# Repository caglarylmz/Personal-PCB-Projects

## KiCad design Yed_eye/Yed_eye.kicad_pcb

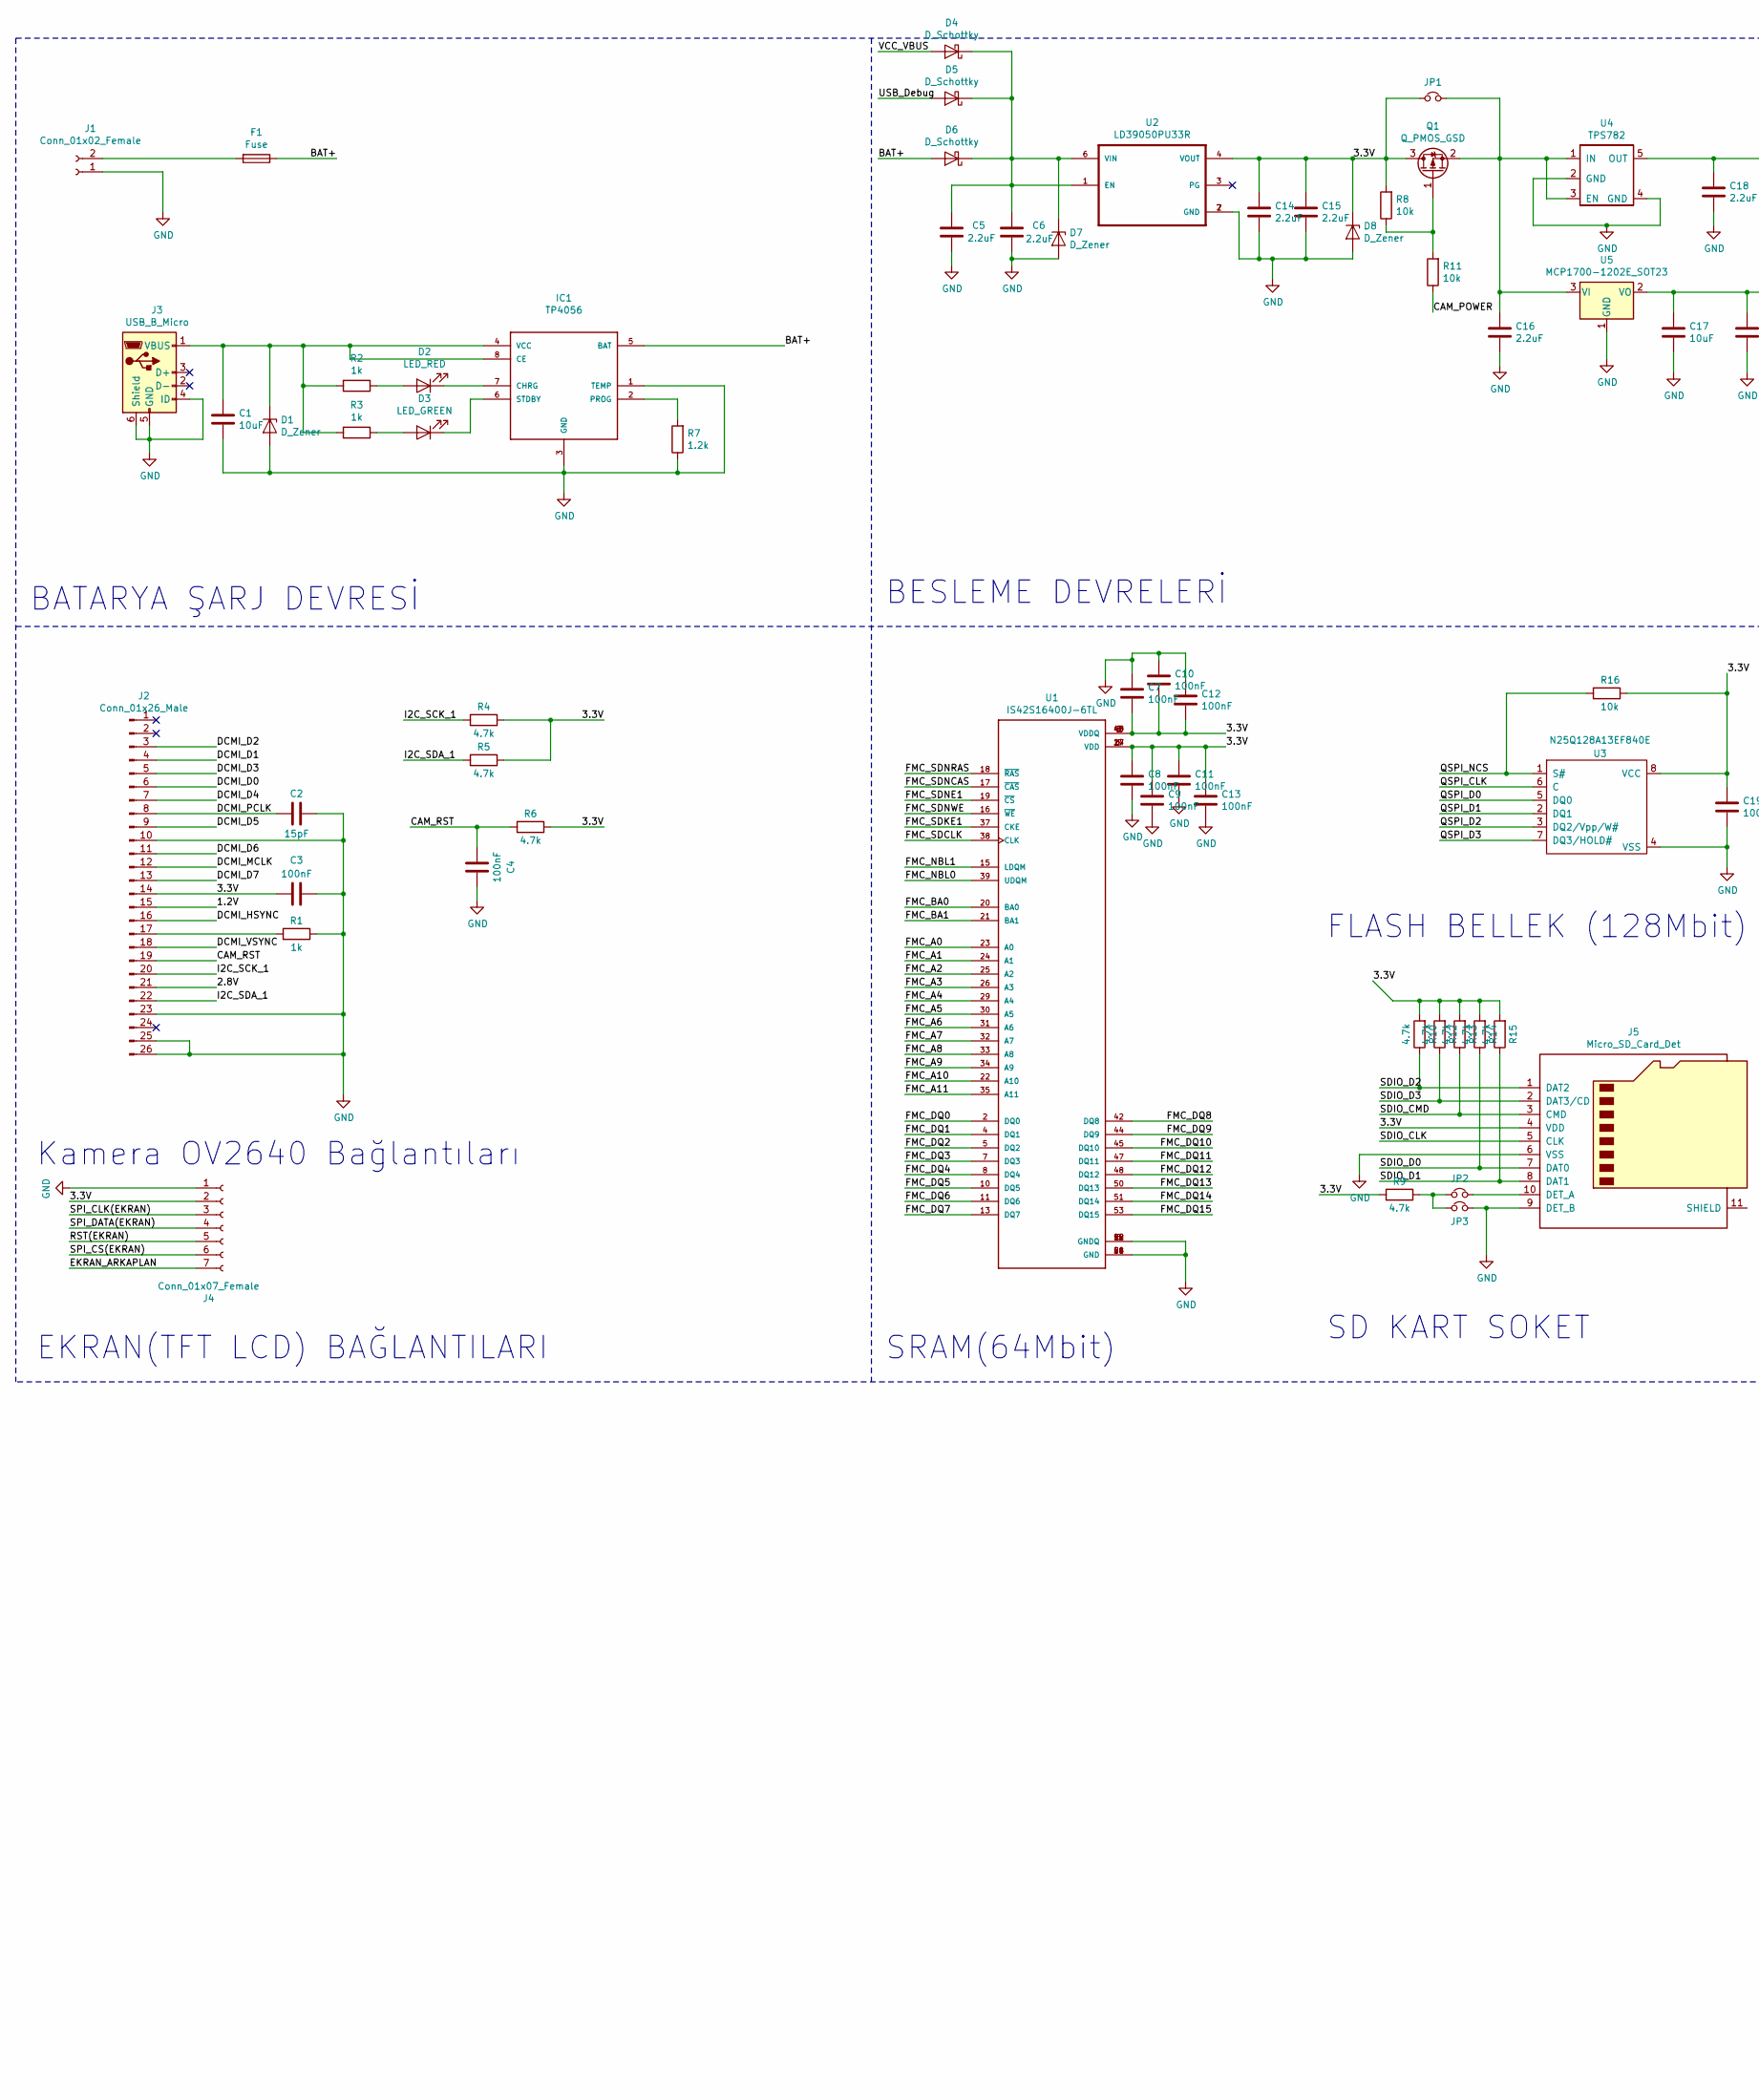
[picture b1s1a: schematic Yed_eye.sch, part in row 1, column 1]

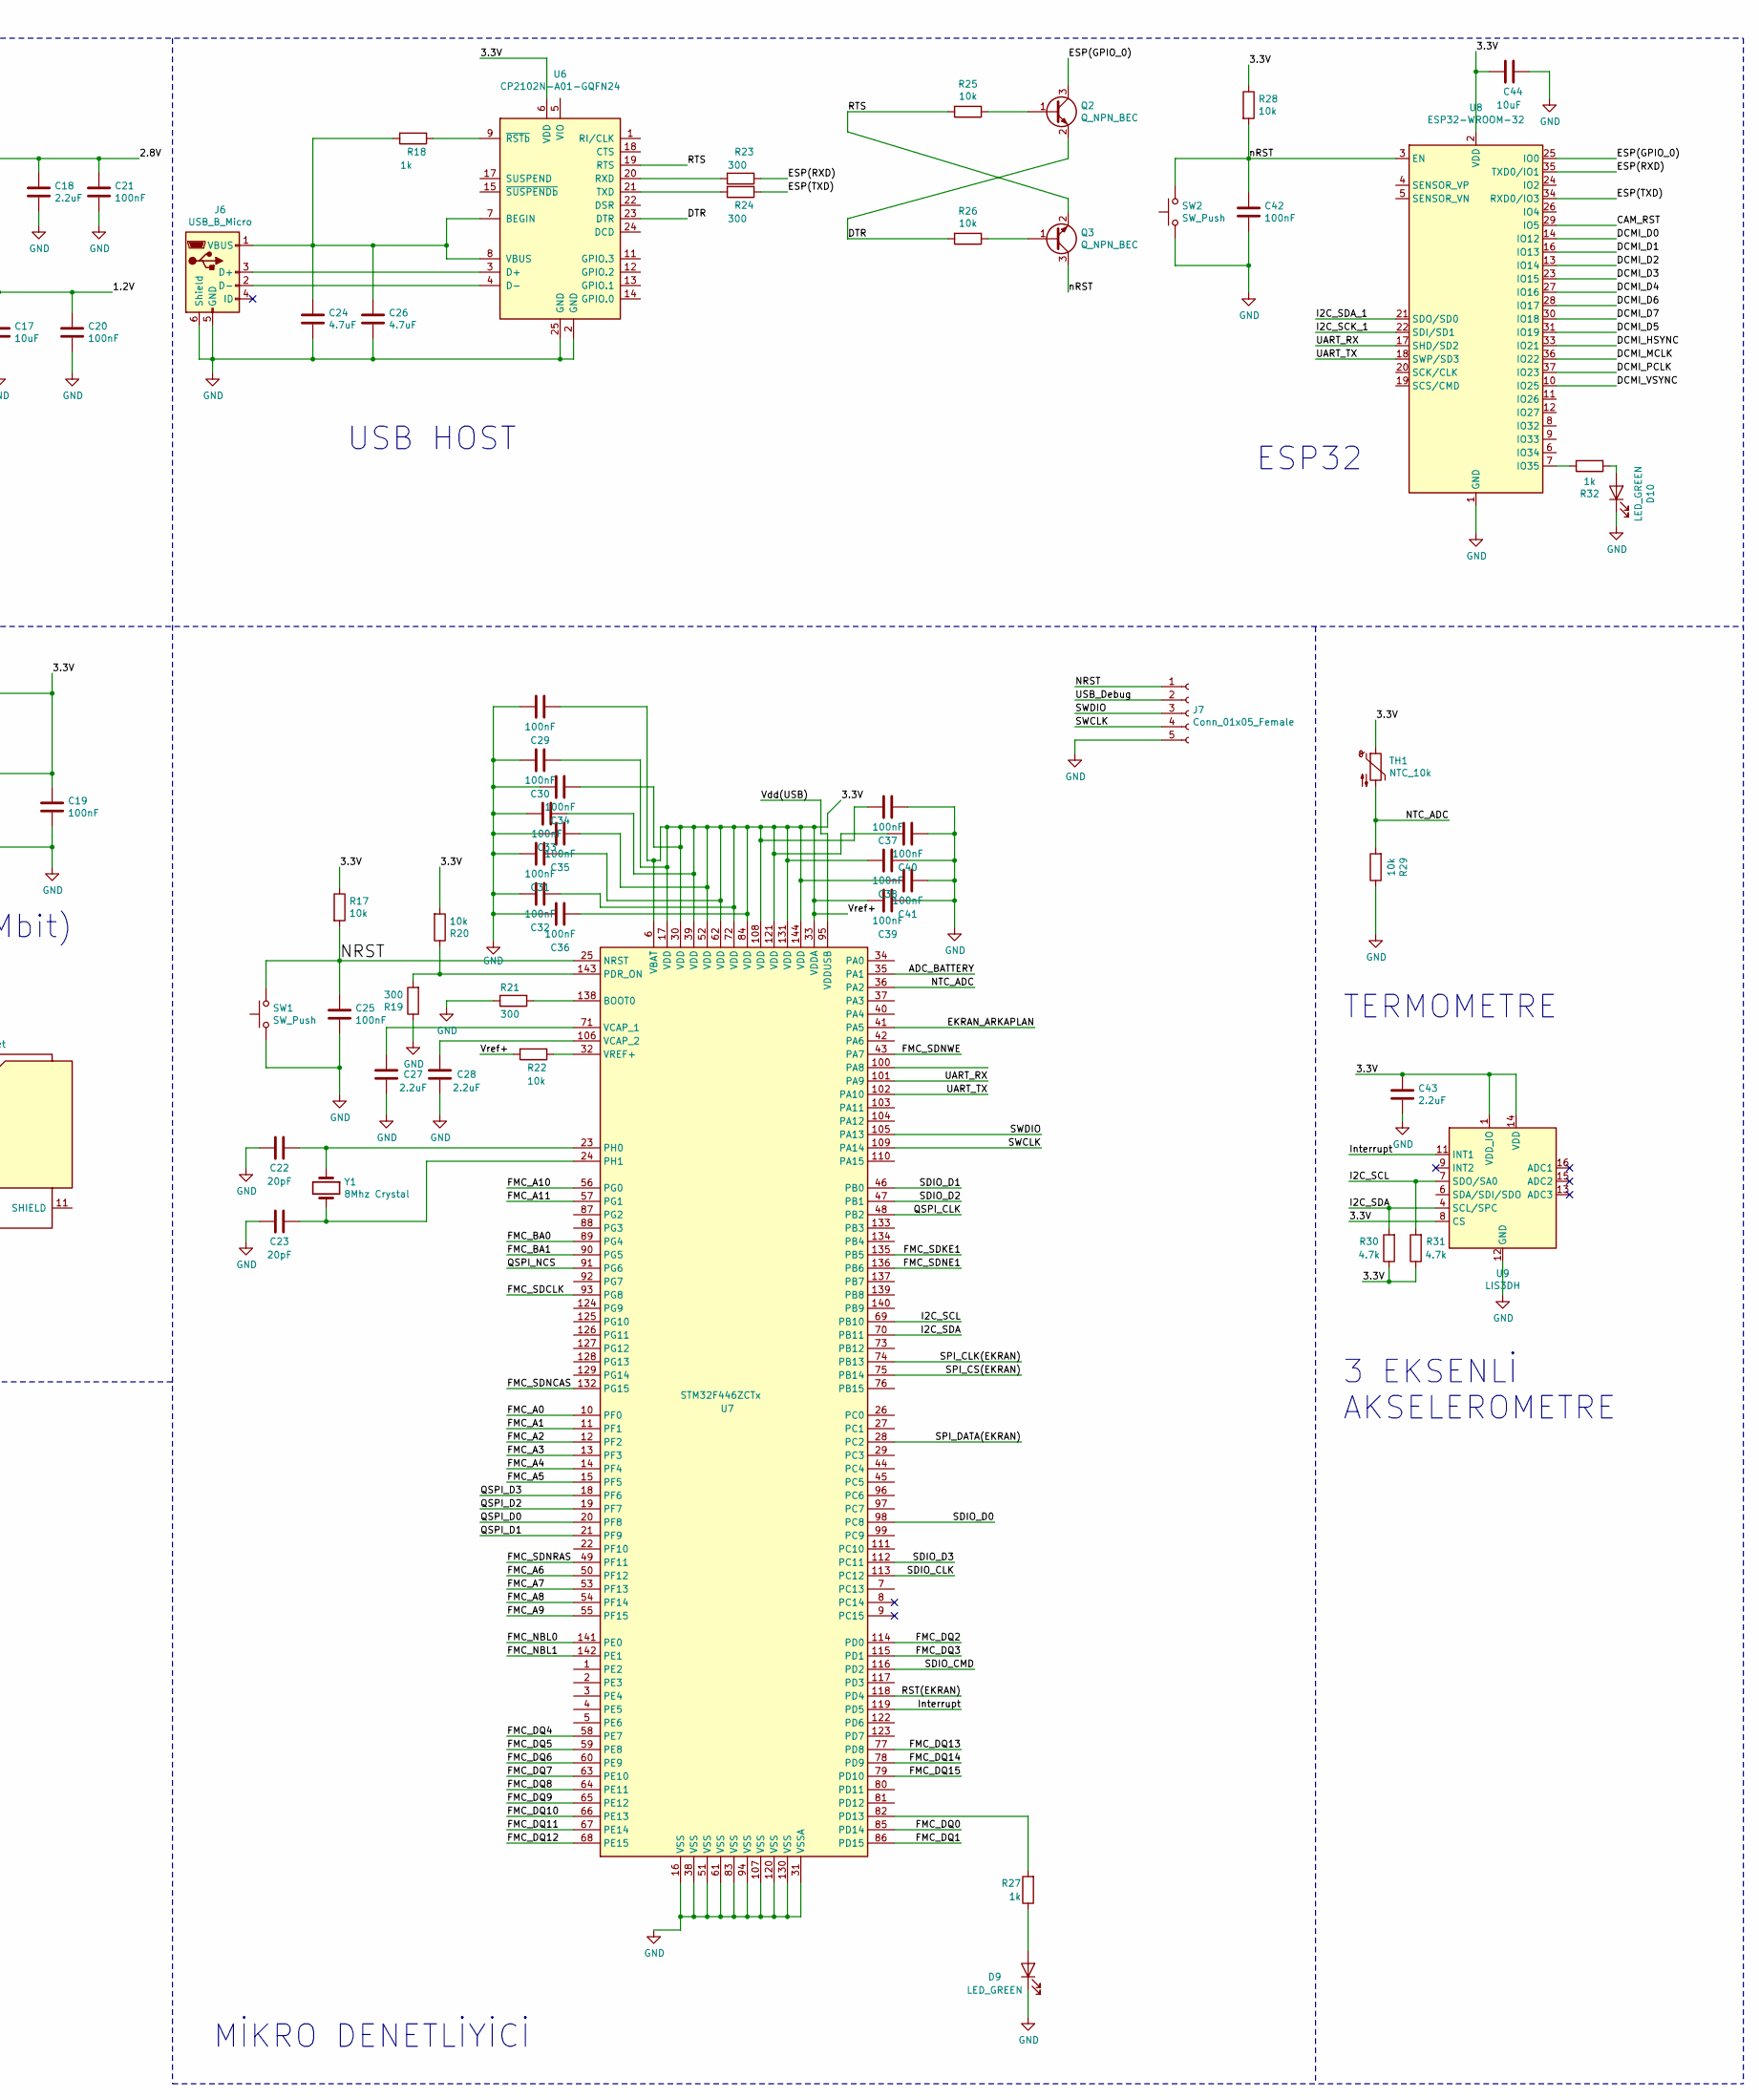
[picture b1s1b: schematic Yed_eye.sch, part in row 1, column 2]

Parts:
C1, C17, C44: 10uF; C_0603_1608Metric_Pad1.05x0.95mm_HandSolder
C2: 15pF; C_0603_1608Metric_Pad1.05x0.95mm_HandSolder
C3, C4, C7, C8, C9, C10, C11, C12, C13, C19, C20, C21, C25, C29, C30, C31, C32, C33, C34, C35, C36, C37, C38, C39, C40, C41, C42: 100nF; C_0603_1608Metric_Pad1.05x0.95mm_HandSolder
C5, C6, C14, C15, C16, C27, C28, C43: 2.2uF; C_0805_2012Metric_Pad1.15x1.40mm_HandSolder
C18: 2.2uF; C_0603_1608Metric_Pad1.05x0.95mm_HandSolder
C22, C23: 20pF; C_0603_1608Metric_Pad1.05x0.95mm_HandSolder
C24, C26: 4.7uF; C_0603_1608Metric_Pad1.05x0.95mm_HandSolder
D1, D7, D8: D_Zener; D_SOD-123
D2: LED_RED; LED_0805_2012Metric_Pad1.15x1.40mm_HandSolder
D3, D9, D10: LED_GREEN; LED_0805_2012Metric_Pad1.15x1.40mm_HandSolder
D4, D5, D6: D_Schottky; D_SOD-123
F1: Fuse; Fuse_1812_4532Metric_Pad1.30x3.40mm_HandSolder
IC1: TP4056; SOP-8_3.76x4.96mm_P1.27mm
J1: Conn_01x02_Female; AMASS_XT30U-F_1x02_P5.0mm_Vertical
J2: Conn_01x26_Male; Hirose_FH12-26S-0.5SH_1x26-1MP_P0.50mm_Horizontal
J3, J6: USB_B_Micro; USB_Micro-B_Molex-105133-0031
J4: Conn_01x07_Female; Molex_200528-0070_1x07-1MP_P1.00mm_Horizontal
J5: Micro_SD_Card_Det; microSD_HC_Hirose_DM3D-SF
J7: Conn_01x05_Female; PinSocket_2x03_P1.27mm_Vertical_SMD
JP1, JP2, JP3: Jumper_NC_Small; SolderJumper-2_P1.3mm_Open_TrianglePad1.0x1.5mm
Q1: Q_PMOS_GSD; SOT-23
Q2, Q3: Q_NPN_BEC; SOT-23
R1, R2, R3, R18, R27, R32: 1k; R_0603_1608Metric_Pad1.05x0.95mm_HandSolder
R4, R5, R6, R9, R10, R12, R13, R14, R15, R30, R31: 4.7k; R_0603_1608Metric_Pad1.05x0.95mm_HandSolder
R7: 1.2k; R_0603_1608Metric_Pad1.05x0.95mm_HandSolder
R8, R11, R16, R17, R20, R22, R25, R26, R28, R29: 10k; R_0603_1608Metric_Pad1.05x0.95mm_HandSolder
R19, R21, R23, R24: 300; R_0603_1608Metric_Pad1.05x0.95mm_HandSolder
SW1: SW_Push; SW_PUSH_6mm_H4.3mm
SW2: SW_Push; SW_PUSH_6mm_H5mm
TH1: NTC_10k; R_0603_1608Metric_Pad1.05x0.95mm_HandSolder
U1: IS42S16400J-6TL; SOP80P1176X120-54N
U2: LD39050PU33R; DFN-6-1EP_3x3mm_P1mm_EP1.5x2.4mm
U3: N25Q128A13EF840E; DFN-8-1EP_6x5mm_P1.27mm_EP2x2mm
U4: TPS782; SOT-23-5_HandSoldering
U5: MCP1700-1202E_SOT23; SOT-23
U6: CP2102N-A01-GQFN24; QFN-24-1EP_4x4mm_P0.5mm_EP2.6x2.6mm
U7: STM32F446ZCTx; LQFP-144_20x20mm_P0.5mm
U8: ESP32-WROOM-32
U9: LIS3DH; LGA-16_3x3mm_P0.5mm_LayoutBorder3x5y
Y1: 8Mhz Crystal; Crystal_SMD_3215-2Pin_3.2x1.5mm

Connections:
/1.2V: C17.1, C20.1, J2.15, U5.2 (VO)
/2.8V: C18.1, C21.1, J2.21, U4.5 (OUT)
/3.3V: C3.2, C7.2, C8.1, C9.1, C10.2, C11.1, C12.2, C13.1, C14.1, C15.1, C19.1, C29.2, C30.2, C31.2, C32.2, C33.2, C34.2, C35.2, C36.2, C37.1, C38.1, C39.1, C40.1, C41.1, C43.1, C44.2, D8.1 (K), J2.14, J4.2, J5.4 (VDD), JP1.1, Q1.3 (D), R4.1, R5.1, R6.1, R8.2, R9.2, R10.2, R12.2, R13.2, R14.2, R15.2, R16.1, R17.1, R20.2, R22.2, R28.1, R30.1, R31.1, TH1.1, U1.1 (VDD), U1.3 (VDDQ), U1.9 (VDDQ), U1.14 (VDD), U1.27 (VDD), U1.43 (VDDQ), U1.49 (VDDQ), U2.4 (VOUT), U3.8 (VCC), U6.6 (VDD), U7.6 (VBAT), U7.17 (VDD), U7.30 (VDD), U7.33 (VDDA), U7.39 (VDD), U7.52 (VDD), U7.62 (VDD), U7.72 (VDD), U7.84 (VDD), U7.108 (VDD), U7.121 (VDD), U7.131 (VDD), U7.144 (VDD), U8.2 (VDD), U9.1 (VDD_IO), U9.8 (CS), U9.14 (VDD)
/BAT+: D6.2 (A), F1.1, IC1.5 (BAT)
/CAM_RST: C4.2, J2.19, R6.2, U8.29 (IO5)
/DCMI_D0: J2.6, U8.14 (IO12)
/DCMI_D1: J2.4, U8.16 (IO13)
/DCMI_D2: J2.3, U8.13 (IO14)
/DCMI_D3: J2.5, U8.23 (IO15)
/DCMI_D4: J2.7, U8.27 (IO16)
/DCMI_D5: J2.9, U8.31 (IO19)
/DCMI_D6: J2.11, U8.28 (IO17)
/DCMI_D7: J2.13, U8.30 (IO18)
/DCMI_HSYNC: J2.16, U8.33 (IO21)
/DCMI_MCLK: J2.12, U8.36 (IO22)
/DCMI_PCLK: C2.2, J2.8, U8.37 (IO23)
/DCMI_VSYNC: J2.18, U8.10 (IO25)
/DTR: Q2.2 (E), R26.2, U6.23 (DTR)
/EKRAN_ARKAPLAN: J4.7, U7.41 (PA5)
/ESP(GPIO_0): Q2.3 (C), U8.25 (IO0)
/ESP(RXD): R23.1, U8.35 (TXD0/IO1)
/ESP(TXD): R24.1, U8.34 (RXD0/IO3)
/FMC_A0: U1.23 (A0), U7.10 (PF0)
/FMC_A1: U1.24 (A1), U7.11 (PF1)
/FMC_A2: U1.25 (A2), U7.12 (PF2)
/FMC_A3: U1.26 (A3), U7.13 (PF3)
/FMC_A4: U1.29 (A4), U7.14 (PF4)
/FMC_A5: U1.30 (A5), U7.15 (PF5)
/FMC_A6: U1.31 (A6), U7.50 (PF12)
/FMC_A7: U1.32 (A7), U7.53 (PF13)
/FMC_A8: U1.33 (A8), U7.54 (PF14)
/FMC_A9: U1.34 (A9), U7.55 (PF15)
/FMC_A10: U1.22 (A10), U7.56 (PG0)
/FMC_A11: U1.35 (A11), U7.57 (PG1)
/FMC_BA0: U1.20 (BA0), U7.89 (PG4)
/FMC_BA1: U1.21 (BA1), U7.90 (PG5)
/FMC_DQ0: U1.2 (DQ0), U7.85 (PD14)
/FMC_DQ1: U1.4 (DQ1), U7.86 (PD15)
/FMC_DQ2: U1.5 (DQ2), U7.114 (PD0)
/FMC_DQ3: U1.7 (DQ3), U7.115 (PD1)
/FMC_DQ4: U1.8 (DQ4), U7.58 (PE7)
/FMC_DQ5: U1.10 (DQ5), U7.59 (PE8)
/FMC_DQ6: U1.11 (DQ6), U7.60 (PE9)
/FMC_DQ7: U1.13 (DQ7), U7.63 (PE10)
/FMC_DQ8: U1.42 (DQ8), U7.64 (PE11)
/FMC_DQ9: U1.44 (DQ9), U7.65 (PE12)
/FMC_DQ10: U1.45 (DQ10), U7.66 (PE13)
/FMC_DQ11: U1.47 (DQ11), U7.67 (PE14)
/FMC_DQ12: U1.48 (DQ12), U7.68 (PE15)
/FMC_DQ13: U1.50 (DQ13), U7.77 (PD8)
/FMC_DQ14: U1.51 (DQ14), U7.78 (PD9)
/FMC_DQ15: U1.53 (DQ15), U7.79 (PD10)
/FMC_NBL0: U1.39 (UDQM), U7.141 (PE0)
/FMC_NBL1: U1.15 (LDQM), U7.142 (PE1)
/FMC_SDCLK: U1.38 (CLK), U7.93 (PG8)
/FMC_SDKE1: U1.37 (CKE), U7.135 (PB5)
/FMC_SDNCAS: U1.17 (~CAS~), U7.132 (PG15)
/FMC_SDNE1: U1.19 (~CS~), U7.136 (PB6)
/FMC_SDNRAS: U1.18 (~RAS~), U7.49 (PF11)
/FMC_SDNWE: U1.16 (~WE~), U7.43 (PA7)
/I2C_SCK_1: J2.20, R4.2, U8.22 (SDI/SD1)
/I2C_SCL: R31.2, U7.69 (PB10), U9.7 (SDO/SA0)
/I2C_SDA: R30.2, U7.70 (PB11), U9.4 (SCL/SPC)
/I2C_SDA_1: J2.22, R5.2, U8.21 (SDO/SD0)
/Interrupt: U7.119 (PD5), U9.11 (INT1)
/NRST: C25.1, J7.1, R17.2, SW1.2, U7.25 (NRST)
/NTC_ADC: R29.2, TH1.2, U7.36 (PA2)
/QSPI_CLK: U3.6 (C), U7.48 (PB2)
/QSPI_D0: U3.5 (DQ0), U7.20 (PF8)
/QSPI_D1: U3.2 (DQ1), U7.21 (PF9)
/QSPI_D2: U3.3 (DQ2/Vpp/W#), U7.19 (PF7)
/QSPI_D3: U3.7 (DQ3/HOLD#), U7.18 (PF6)
/QSPI_NCS: R16.2, U3.1 (S#), U7.91 (PG6)
/RST(EKRAN): J4.5, U7.118 (PD4)
/RTS: Q3.2 (E), R25.2, U6.19 (RTS)
/SDIO_CLK: J5.5 (CLK), U7.113 (PC12)
/SDIO_CMD: J5.3 (CMD), R13.1, U7.116 (PD2)
/SDIO_D0: J5.7 (DAT0), R14.1, U7.98 (PC8)
/SDIO_D1: J5.8 (DAT1), R15.1, U7.46 (PB0)
/SDIO_D2: J5.1 (DAT2), R10.1, U7.47 (PB1)
/SDIO_D3: J5.2 (DAT3/CD), R12.1, U7.112 (PC11)
/SPI_CLK(EKRAN): J4.3, U7.74 (PB13)
/SPI_CS(EKRAN): J4.6, U7.75 (PB14)
/SPI_DATA(EKRAN): J4.4, U7.28 (PC2)
/SWCLK: J7.4, U7.109 (PA14)
/SWDIO: J7.3, U7.105 (PA13)
/UART_RX: U7.101 (PA9), U8.17 (SHD/SD2)
/UART_TX: U7.102 (PA10), U8.18 (SWP/SD3)
/USB_Debug: D5.2 (A), J7.2
/nRST: C42.1, Q3.3 (C), R28.2, SW2.2, U8.3 (EN)
GND: C1.2, C2.1, C3.1, C4.1, C5.2, C6.2, C7.1, C8.2, C9.2, C10.1, C11.2, C12.1, C13.2, C14.2, C15.2, C16.2, C17.2, C18.2, C19.2, C20.2, C21.2, C22.2, C23.2, C24.2, C25.2, C26.2, C27.2, C28.2, C29.1, C30.1, C31.1, C32.1, C33.1, C34.1, C35.1, C36.1, C37.2, C38.2, C39.2, C40.2, C41.2, C42.2, C43.2, C44.1, D1.2 (A), D7.2 (A), D8.2 (A), D9.1 (K), D10.1 (K), IC1.1 (TEMP), IC1.3 (GND), J1.1, J2.10, J2.23, J2.25, J2.26, J3.4 (ID), J3.5 (GND), J3.6 (Shield), J4.1, J5.6 (VSS), J5.9 (DET_B), J6.5 (GND), J6.6 (Shield), J7.5, JP3.2, R1.1, R7.1, R19.1, R21.1, R29.1, SW1.1, SW2.1, U1.6 (GNDQ), U1.12 (GNDQ), U1.28 (GND), U1.41 (GND), U1.46 (GNDQ), U1.52 (GNDQ), U1.54 (GND), U2.2 (GND), U2.7 (GND), U3.4 (VSS), U4.2 (GND), U4.4 (GND), U5.1 (GND), U6.2 (GND), U6.25 (GND), U7.16 (VSS), U7.31 (VSSA), U7.38 (VSS), U7.51 (VSS), U7.61 (VSS), U7.83 (VSS), U7.94 (VSS), U7.107 (VSS), U7.120 (VSS), U7.130 (VSS), U8.1 (GND), U8.15 (GND), U8.38 (GND), U9.5 (GND), U9.10 (GND), U9.12 (GND)
unnamed: C1.1, D1.1 (K), IC1.4 (VCC), IC1.8 (CE), J3.1 (VBUS), R2.2, R3.2
unnamed: C5.1, C6.1, D4.1 (K), D5.1 (K), D6.1 (K), D7.1 (K), U2.1 (EN), U2.6 (VIN)
unnamed: C16.1, JP1.2, Q1.2 (S), U4.1 (IN), U4.3 (EN), U5.3 (VI)
unnamed: C22.1, U7.23 (PH0), Y1.1
unnamed: C23.1, U7.24 (PH1), Y1.2
unnamed: C24.1, C26.1, J6.1 (VBUS), R18.2, U6.7 (BEGIN), U6.8 (VBUS)
unnamed: C27.1, U7.71 (VCAP_1)
unnamed: C28.1, U7.106 (VCAP_2)
unnamed: D2.1 (K), IC1.7 (CHRG)
unnamed: D2.2 (A), R2.1
unnamed: D3.1 (K), IC1.6 (STDBY)
unnamed: D3.2 (A), R3.1
unnamed: D9.2 (A), R27.1
unnamed: D10.2 (A), R32.2
unnamed: F1.2, J1.2
unnamed: IC1.2 (PROG), R7.2
unnamed: J2.17, R1.2
unnamed: J5.10 (DET_A), JP2.2
unnamed: J6.2 (D-), U6.4 (D-)
unnamed: J6.3 (D+), U6.3 (D+)
unnamed: JP2.1, JP3.1, R9.1
unnamed: Q1.1 (G), R8.1, R11.2
unnamed: Q2.1 (B), R25.1
unnamed: Q3.1 (B), R26.1
unnamed: R18.1, U6.9 (~RSTb)
unnamed: R19.2, R20.1, U7.143 (PDR_ON)
unnamed: R21.2, U7.138 (BOOT0)
unnamed: R22.1, U7.32 (VREF+)
unnamed: R23.2, U6.20 (RXD)
unnamed: R24.2, U6.21 (TXD)
unnamed: R27.2, U7.82 (PD13)
unnamed: R32.1, U8.7 (IO35)

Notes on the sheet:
Kamera OV2640 Bağlantıları
FLASH BELLEK (128Mbit)
SRAM(64Mbit)
BATARYA ŞARJ DEVRESİ
BESLEME DEVRELERİ
USB HOST
SD KART SOKET
MİKRO DENETLİYİCİ
TERMOMETRE
3 EKSENLİ AKSELEROMETRE
ESP32
EKRAN(TFT LCD) BAĞLANTILARI

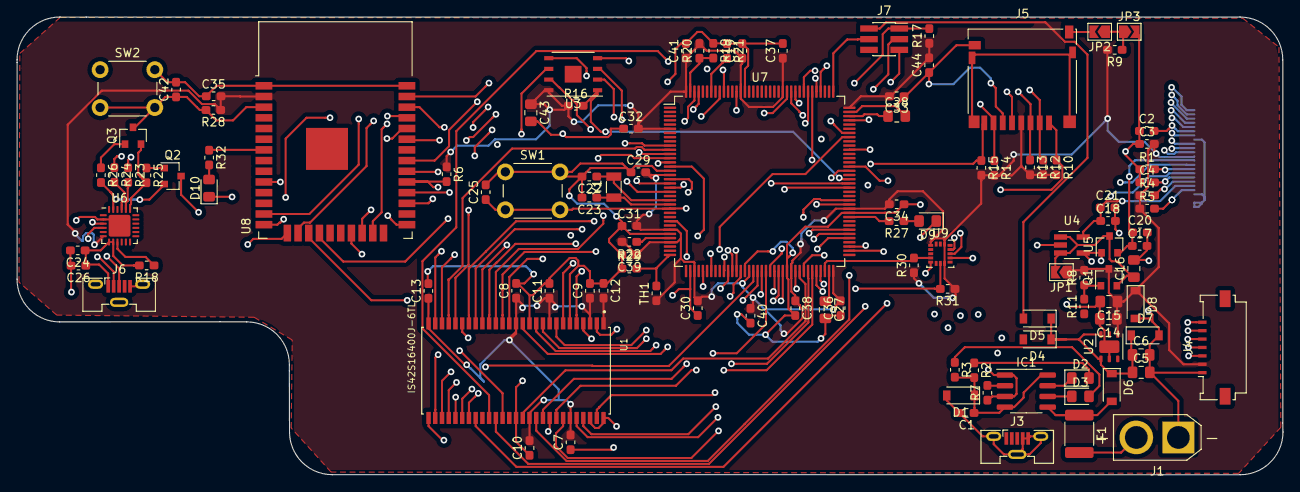
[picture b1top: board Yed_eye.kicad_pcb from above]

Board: 4 copper layers, 150.5 x 54.4 mm, 114 parts (1 on the bottom side), 123 nets.

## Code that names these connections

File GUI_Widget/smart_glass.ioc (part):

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Mcu.Name=STM32F446Z(C-E)Tx
Mcu.Package=LQFP144
Mcu.UserName=STM32F446ZCTx
PA1.GPIOParameters=GPIO_Label
PA1.GPIO_Label=ADC_BAT
PA1.Signal=ADCx_IN1
PA10.Mode=Asynchronous
PA10.Signal=USART1_RX
PA13.Mode=Serial_Wire
PA13.Signal=SYS_JTMS-SWDIO
PA14.Mode=Serial_Wire
PA14.Signal=SYS_JTCK-SWCLK
PA2.GPIOParameters=GPIO_Label
PA2.GPIO_Label=ADC_NTC
PA2.Signal=ADCx_IN2
PA4.Mode=Slave_8_bits_External_Synchro
PA4.Signal=DCMI_HSYNC
PA5.Signal=COMP_DAC2_group
PA6.Mode=Slave_8_bits_External_Synchro
PA6.Signal=DCMI_PIXCLK
PA7.Signal=FMC_SDNWE
PA8.Mode=Clock-out-1
PA8.Signal=RCC_MCO_1
PA9.Mode=Asynchronous
PA9.Signal=USART1_TX
PB0.Mode=SD_4_bits_Wide_bus
PB0.Signal=SDIO_D1
PB1.Mode=SD_4_bits_Wide_bus
PB1.Signal=SDIO_D2
PB10.Mode=I2C
PB10.Signal=I2C2_SCL
PB11.Mode=I2C
PB11.Signal=I2C2_SDA
PB13.Mode=Full_Duplex_Master
PB13.Signal=SPI2_SCK
PB2.Mode=Single Bank 1
PB2.Signal=QUADSPI_CLK
PB5.Mode=SdramChipSelect2_1
PB5.Signal=FMC_SDCKE1
PB6.Mode=SdramChipSelect2_1
PB6.Signal=FMC_SDNE1
PB7.Mode=I2C
PB7.Signal=I2C1_SDA
PB8.Mode=I2C
PB8.Signal=I2C1_SCL
PC1.Mode=Full_Duplex_Master
PC1.Signal=SPI2_MOSI
PC11.Mode=SD_4_bits_Wide_bus
PC11.Signal=SDIO_D3
PC12.Mode=SD_4_bits_Wide_bus
PC12.Signal=SDIO_CK
PC14-OSC32_IN.Mode=LSE-External-Clock-Source
PC14-OSC32_IN.Signal=RCC_OSC32_IN
PC15-OSC32_OUT.Mode=LSE-External-Clock-Source
PC15-OSC32_OUT.Signal=RCC_OSC32_OUT
PC2.Mode=Full_Duplex_Master
PC2.Signal=SPI2_MISO
PC3.GPIOParameters=GPIO_Label
PC3.GPIO_Label=SPI_CS
PC3.Signal=GPIO_Output
PC6.Mode=Slave_8_bits_External_Synchro
PC6.Signal=DCMI_D0
PC7.Mode=Slave_8_bits_External_Synchro
PC7.Signal=DCMI_D1
PC8.Mode=SD_4_bits_Wide_bus
PC8.Signal=SDIO_D0
PC9.Mode=Slave_8_bits_External_Synchro
PC9.Signal=DCMI_D3
PD0.Signal=FMC_D2_DA2
PD1.Signal=FMC_D3_DA3
PD10.Signal=FMC_D15_DA15
PD12.GPIOParameters=GPIO_Label
PD12.GPIO_Label=LED2
PD12.Signal=GPIO_Output
PD13.GPIOParameters=GPIO_Label
PD13.GPIO_Label=LED1
PD13.Signal=GPIO_Output
PD14.Signal=FMC_D0_DA0
PD15.Signal=FMC_D1_DA1
PD2.Mode=SD_4_bits_Wide_bus
PD2.Signal=SDIO_CMD
PD3.Mode=Slave_8_bits_External_Synchro
PD3.Signal=DCMI_D5
PD4.GPIOParameters=GPIO_Label
PD4.GPIO_Label=EKRAN_RST
PD4.Signal=GPIO_Output
PD5.GPIOParameters=GPIO_Label
PD5.GPIO_Label=MEMS_INT
PD5.Signal=GPXTI5
PD8.Signal=FMC_D13_DA13
PD9.Signal=FMC_D14_DA14
PE0.Signal=FMC_NBL0
PE1.Signal=FMC_NBL1
PE10.Signal=FMC_D7_DA7
PE11.Signal=FMC_D8_DA8
PE12.Signal=FMC_D9_DA9
PE13.Signal=FMC_D10_DA10
PE14.Signal=FMC_D11_DA11
PE15.Signal=FMC_D12_DA12
PE3.GPIOParameters=GPIO_Label
PE3.GPIO_Label=CAM_RST
PE3.Signal=GPIO_Output
PE4.Mode=Slave_8_bits_External_Synchro
PE4.Signal=DCMI_D4
PE5.Mode=Slave_8_bits_External_Synchro
PE5.Signal=DCMI_D6
PE6.Mode=Slave_8_bits_External_Synchro
PE6.Signal=DCMI_D7
PE7.Signal=FMC_D4_DA4
PE8.Signal=FMC_D5_DA5
PE9.Signal=FMC_D6_DA6
PF0.Signal=FMC_A0
PF1.Signal=FMC_A1
PF11.Signal=FMC_SDNRAS
PF12.Signal=FMC_A6
PF13.Signal=FMC_A7
PF14.Signal=FMC_A8
PF15.Signal=FMC_A9
PF2.Signal=FMC_A2
PF3.Signal=FMC_A3
PF4.Signal=FMC_A4
PF5.Signal=FMC_A5
PF6.Mode=Single Bank 1
PF6.Signal=QUADSPI_BK1_IO3
PF7.Mode=Single Bank 1
PF7.Signal=QUADSPI_BK1_IO2
PF8.Mode=Single Bank 1
PF8.Signal=QUADSPI_BK1_IO0
PF9.Mode=Single Bank 1
PF9.Signal=QUADSPI_BK1_IO1
PG0.Signal=FMC_A10
PG1.Signal=FMC_A11
PG10.Mode=Slave_8_bits_External_Synchro
PG10.Signal=DCMI_D2
PG15.Signal=FMC_SDNCAS
PG4.Signal=FMC_A14_BA0
PG5.Signal=FMC_A15_BA1
PG6.Mode=Single Bank 1
PG6.Signal=QUADSPI_BK1_NCS
PG8.Signal=FMC_SDCLK
PG9.Mode=Slave_8_bits_External_Synchro
PG9.Signal=DCMI_VSYNC
PH0-OSC_IN.Mode=HSE-External-Oscillator
PH0-OSC_IN.Signal=RCC_OSC_IN
PH1-OSC_OUT.Mode=HSE-External-Oscillator
PH1-OSC_OUT.Signal=RCC_OSC_OUT
RCC.SYSCLKFreq_VALUE=180000000
RCC.SYSCLKSource=RCC_SYSCLKSOURCE_PLLCLK
board=custom

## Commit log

2020-04-23 Creating Widget in STM32F746VGT
2020-04-23 test file deleted
2020-04-24 file has been sent to repo
2020-05-19 Finishing project added
2020-05-19 Pin Config added.
2020-05-19 Shematic added
